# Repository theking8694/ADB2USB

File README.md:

# ADB2USB
An Apple ADB to USB adapter for QMK using the ATMega32U2, featuring USB-C!
One of the projects I used as an intro to KiCad

Probably not the simplest, but follows what is said for the 32U2 datasheet.

Tested working, highly suggest a 32U2 with DFU bootloader flashed (DigiKey seems to have them preflashed)
Highly reccomend using hot air instead of an iron.

You can use the online QMK configurator firmware builder to produce a .hex that can be flashed using QMK Toolbox (Arduino will not see the DFU bootloader!)
(Or compile it locally and flash it however you want)

The CSV contains a BOM listing generated by KiCad,
parts I used are listed below:

GRM0335C1E200JA01D (20pF cap), 

CL05A105MQ5NNNC (1uF cap), 

USB4085-GF-A (USB C port), 

RMCF0805FT1K00 (1k resistor), 

WR06X220 JTL (22 resistor), 

ABLS-16.000MHZ-D-3-Y-T (16Mhz crystal), 

M50-3530342 (optinal ISP headers), 

PTS526 SM15 SMTR2 LFS (reset switch), 

RR0816P-512-D (5.1k resistor), 

WR06X103 JTL (10k resistor), 

CUI_MD-40SMK (S-video socket) (yes, S-video),

and, of course, an ATMega32U2(-A)

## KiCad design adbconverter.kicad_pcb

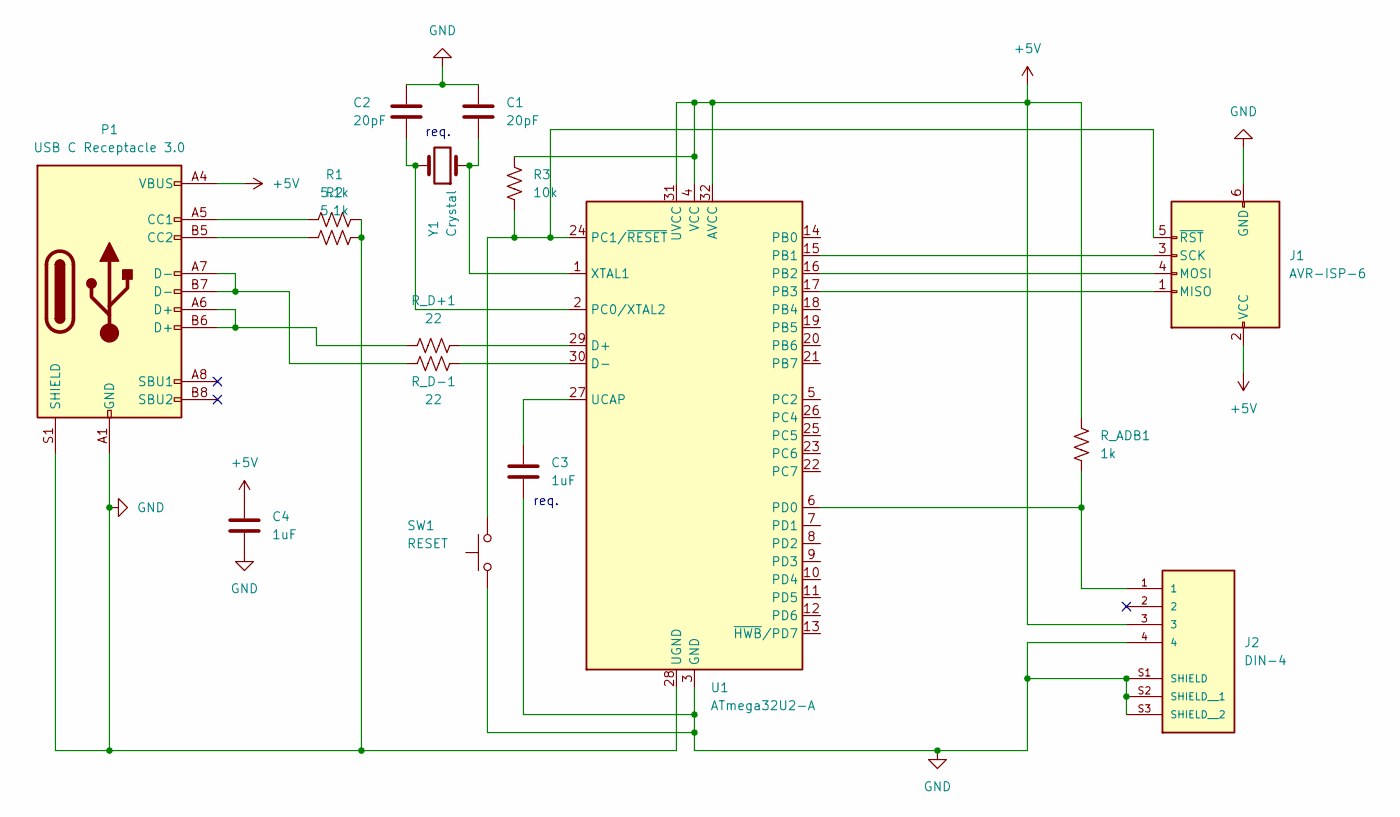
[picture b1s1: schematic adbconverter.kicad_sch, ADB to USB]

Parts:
C1, C2: 20pF; C_0201_0603Metric_Pad0.64x0.40mm_HandSolder
C3, C4: 1uF; C_0402_1005Metric_Pad0.74x0.62mm_HandSolder
J1: AVR-ISP-6; PinHeader_2x03_P1.27mm_Vertical
J2: DIN-4; CUI_MD-40SMK; PART_REV 1.02
P1: USB C Receptacle 3.0; USB_C_Receptacle_GCT_USB4085
R1, R2: 5.1k; R_0603_1608Metric_Pad0.98x0.95mm_HandSolder
R3: 10k; R_0603_1608Metric_Pad0.98x0.95mm_HandSolder
R_ADB1: 1k; R_0805_2012Metric_Pad1.20x1.40mm_HandSolder
R_D+1: 22; R_0603_1608Metric_Pad0.98x0.95mm_HandSolder
R_D-1: 22; R_0603_1608Metric_Pad0.98x0.95mm_HandSolder
SW1: RESET; SW_SPST_SKQG_WithStem
U1: ATmega32U2-A; TQFP-32_7x7mm_P0.8mm
Y1: Crystal; Crystal_SMD_HC49-SD

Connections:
+5V: C4.2, J1.2 (VCC), J2.3, P1.A4 (VBUS), P1.A9 (VBUS), P1.B4 (VBUS), P1.B9 (VBUS), R3.2, R_ADB1.2, U1.4 (VCC), U1.31 (UVCC), U1.32 (AVCC)
GND: C1.2, C2.2, C3.1, C4.1, J1.6 (GND), J2.4, J2.S1 (SHIELD), J2.S2 (SHIELD__1), J2.S3 (SHIELD__2), P1.A1 (GND), P1.A12 (GND), P1.B1 (GND), P1.B12 (GND), P1.S1 (SHIELD), R1.2, R2.2, SW1.1, U1.3 (GND), U1.28 (UGND)
unnamed: J1.1 (MISO), U1.17 (PB3)
unnamed: J1.4 (MOSI), U1.16 (PB2)
unnamed: J1.3 (SCK), U1.15 (PB1)
unnamed: J1.5 (~RST), R3.1, SW1.2, U1.24 (PC1/~RESET)
unnamed: P1.A5 (CC1), R1.1
unnamed: P1.B5 (CC2), R2.1
unnamed: P1.A6 (D+), P1.B6 (D+), R_D+1.1
unnamed: P1.A7 (D-), P1.B7 (D-), R_D-1.1
unnamed: R_D+1.2, U1.29 (D+)
unnamed: R_D-1.2, U1.30 (D-)
unnamed: C2.1, U1.2 (PC0/XTAL2), Y1.2
unnamed: J2.1, R_ADB1.1, U1.6 (PD0)
unnamed: C3.2, U1.27 (UCAP)
unnamed: C1.1, U1.1 (XTAL1), Y1.1

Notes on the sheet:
req.

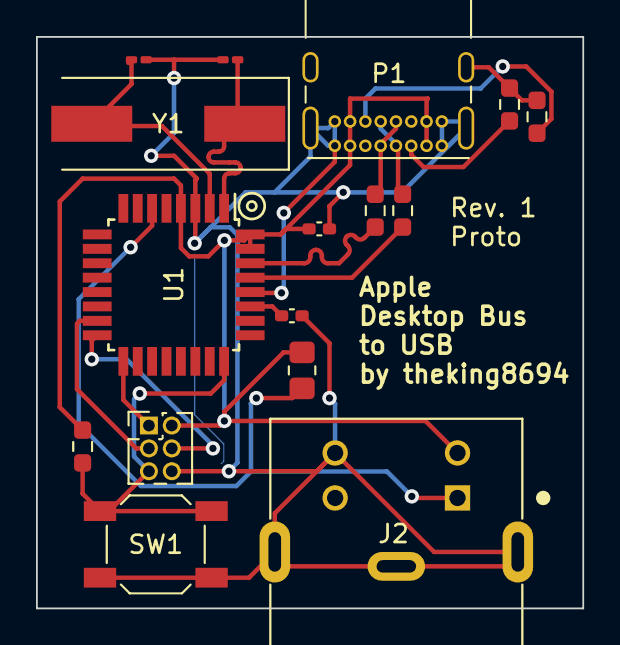
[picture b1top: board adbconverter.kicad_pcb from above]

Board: 2 copper layers, 30.4 x 31.8 mm, 16 parts (0 on the bottom side), 16 nets.

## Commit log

2024-01-03 Update README.md
    add the info that seemed most important
2024-01-03 add BOM, and kicad files
2024-01-03 add parts I used
2024-01-03 firmware info
